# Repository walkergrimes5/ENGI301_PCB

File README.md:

# ENGI301_PCB
PCB design files for ENGI 301 project 2

This project builds on the work I started earlier this year (2018). I am continuing to implement a Octavo PocketBeagle board as the primary flight controller for a 210mm quad copter. The PocketBeagle is not meant specifically for this task, and, as such, is missing several critical components required for flight and autonomous control. Specifically, the board lacks an accelerometer/gyroscope, a altimeter, a GPS connection point, and proper motor headers. The goal of this project is to create a cape for the PocketBeagle that upgrades functionality to include these missing components. The cape fits into the profile of the PocketBeagle and allows it to operate as a flight control board for a quad copter. Eventually, this system should be fully compatible with ArduPilot and be a cheap way to implement a small, autonomous drone.

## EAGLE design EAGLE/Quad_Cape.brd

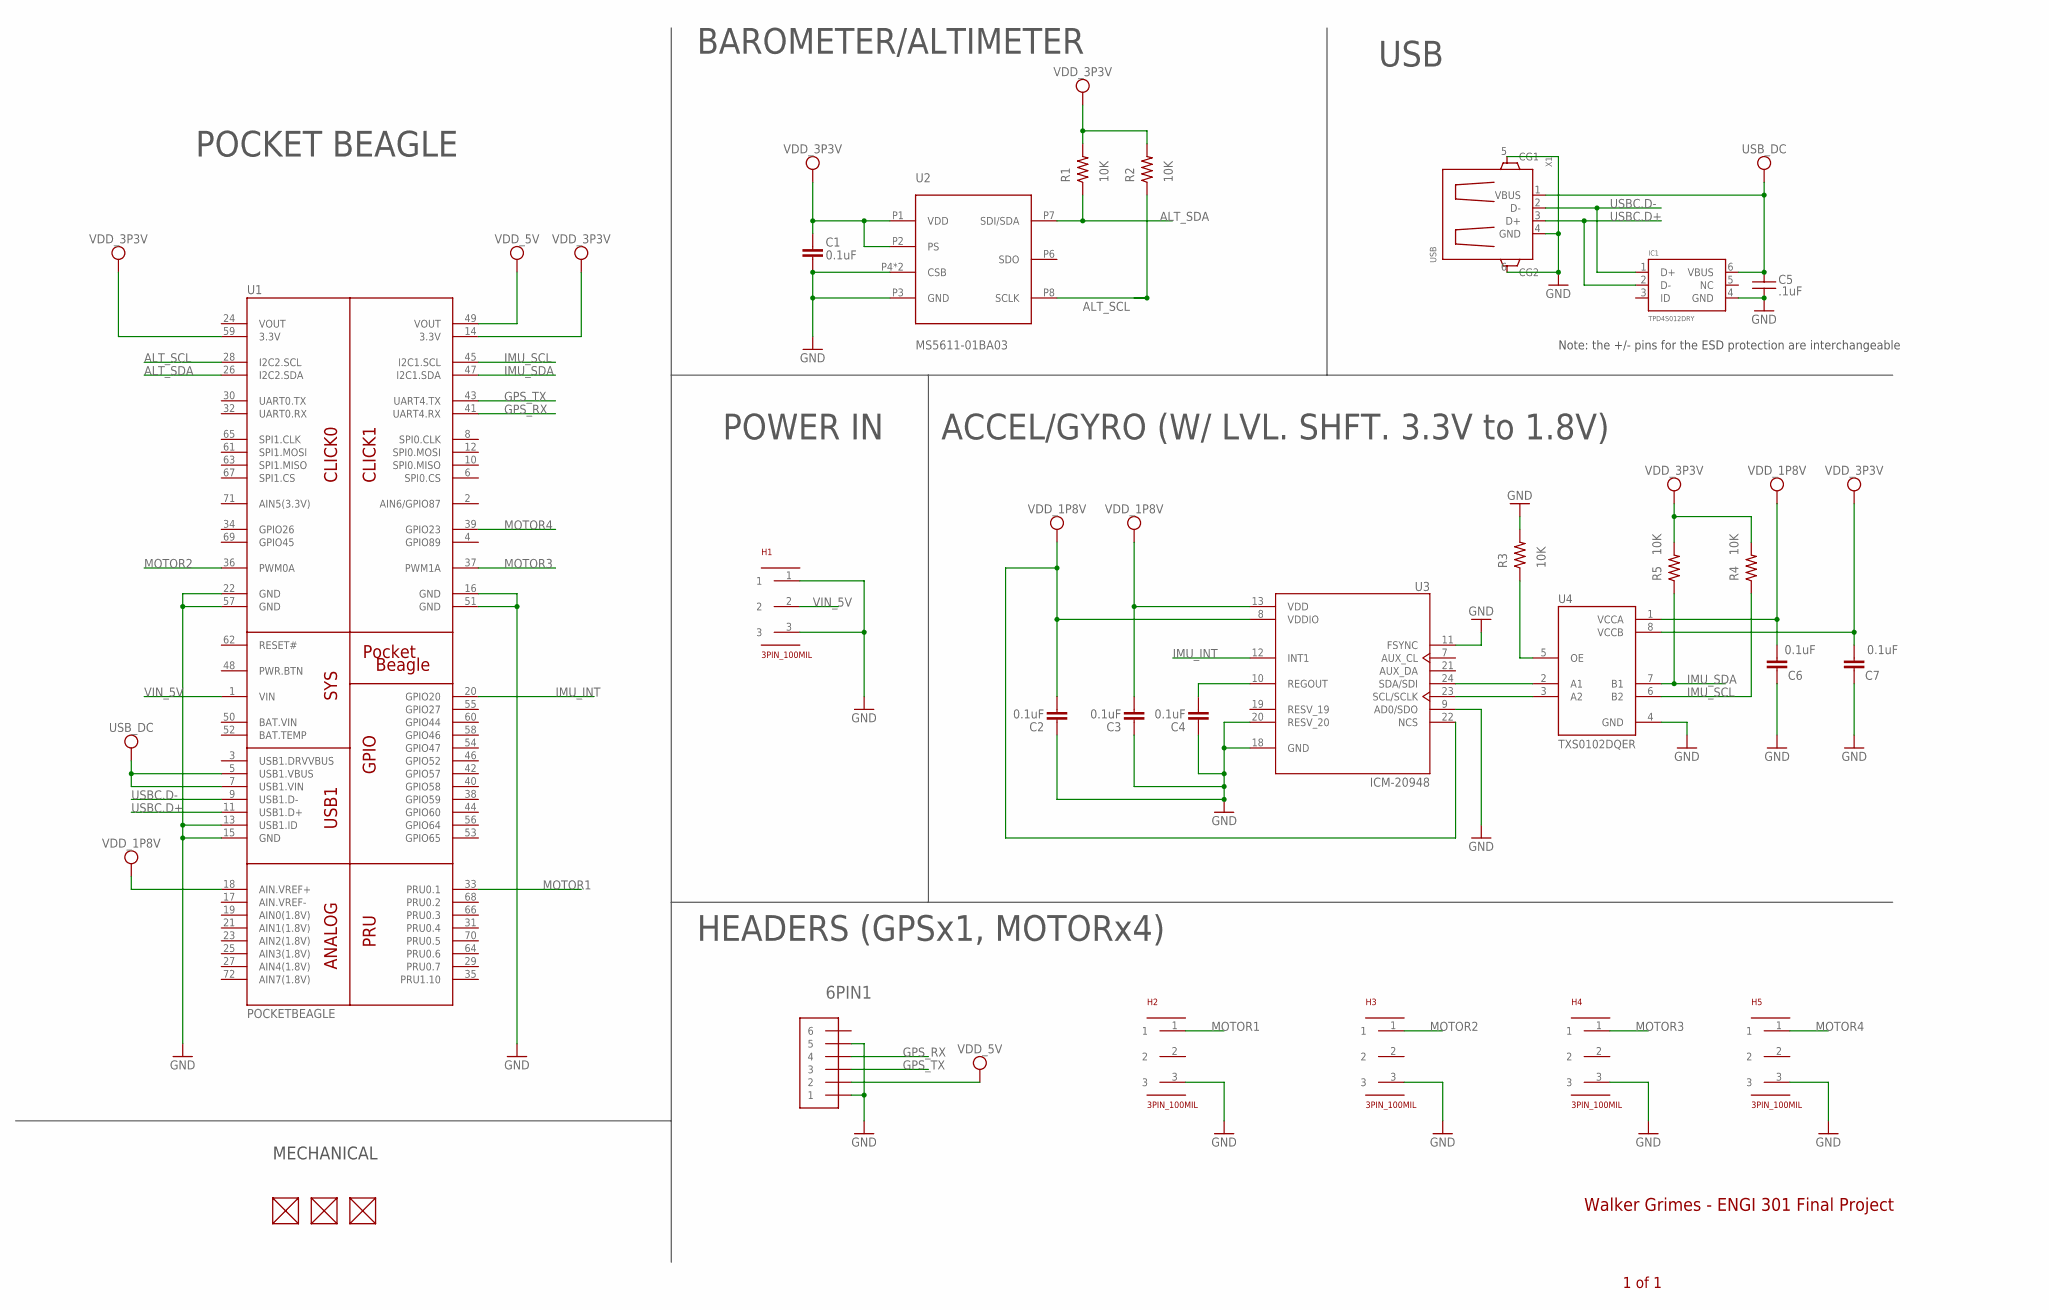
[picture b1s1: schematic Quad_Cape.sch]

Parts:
6PIN1: STRAWSON_EAGLE_LIB_JST_SH_6
C1, C2, C3, C4, C6, C7: 0.1uF; C0603
C5: .1uF; 0402
FUD1, FUD2, FUD3: FIDUCIAL; FIDUCIAL_40MIL
H1, H2, H3, H4, H5: 3PIN_100MIL
IC1: TPD4S012DRY; SON-6(TI)-DRY
R1, R2, R3, R4, R5: 10K; R0603
U1: POCKETBEAGLE
U2: MS5611-01BA03
U3: ICM-20948; QFN40P300X300X105-25N
U4: TXS0102DQER; VOLTAGETRANSLATOR_TXS0102DQER
X1: USB; GHI2_USB_HOST_HORIZONTAL_W/CHASSIS_GND

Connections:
ALT_SCL: R2.1, U1.28 (I2C2.SCL), U2.P8 (SCLK)
ALT_SDA: R1.1, U1.26 (I2C2.SDA), U2.P7 (SDI/SDA)
BAT.VIN: U1.50 (BAT.VIN)
GND: 6PIN1.1, 6PIN1.5, C1.2, C2.1, C3.1, C4.1, C5.2, C6.1, C7.1, H1.1, H1.3, H2.3, H3.3, H4.3, H5.3, IC1.4 (GND), R3.2, U1.13 (USB1.ID), U1.15 (GND), U1.16 (GND), U1.22 (GND), U1.51 (GND), U1.57 (GND), U2.P3 (GND), U2.P4 (CSB), U2.P5 (CSB), U3.9 (AD0/SDO), U3.11 (FSYNC), U3.18 (GND), U3.20 (RESV_20), U4.4 (GND), X1.4 (GND), X1.5 (CG1), X1.6 (CG2)
GPS_RX: 6PIN1.4, U1.41 (UART4.RX)
GPS_TX: 6PIN1.3, U1.43 (UART4.TX)
IMU_INT: U1.20 (GPIO20), U3.12 (INT1)
IMU_SCL: R4.1, U1.45 (I2C1.SCL), U4.6 (B2)
IMU_SDA: R5.1, U1.47 (I2C1.SDA), U4.7 (B1)
MOTOR1: H2.1, U1.33 (PRU0.1)
MOTOR2: H3.1, U1.36 (PWM0A)
MOTOR3: H4.1, U1.37 (PWM1A)
MOTOR4: H5.1, U1.39 (GPIO23)
unnamed: C4.2, U3.10 (REGOUT)
unnamed: R3.1, U4.5 (OE)
unnamed: U3.23 (SCL/SCLK), U4.3 (A2)
unnamed: U3.24 (SDA/SDI), U4.2 (A1)
USBC.D+: IC1.2 (D-), U1.11 (USB1.D+), X1.3 (D+)
USBC.D-: IC1.1 (D+), U1.9 (USB1.D-), X1.2 (D-)
USB_DC: C5.1, IC1.6 (VBUS), U1.5 (USB1.VBUS), U1.7 (USB1.VIN), X1.1 (VBUS)
VDD_1P8V: C2.2, C3.2, C6.2, U1.18 (AIN.VREF+), U3.8 (VDDIO), U3.13 (VDD), U3.22 (NCS), U4.1 (VCCA)
VDD_3P3V: C1.1, C7.2, R1.2, R2.2, R4.2, R5.2, U1.14 (3.3V), U1.59 (3.3V), U2.P1 (VDD), U2.P2 (PS), U4.8 (VCCB)
VDD_5V: 6PIN1.2, U1.49 (VOUT)
VIN_5V: H1.2, U1.1 (VIN)
VOUT: U1.24 (VOUT)

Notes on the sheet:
Walker Grimes - ENGI 301 Final Project
HEADERS (GPSx1, MOTORx4)
BAROMETER/ALTIMETER
USB
ACCEL/GYRO (W/ LVL. SHFT. 3.3V to 1.8V)
POCKET BEAGLE
1 of 1
POWER IN
MECHANICAL
Note: the +/- pins for the ESD protection are interchangeable

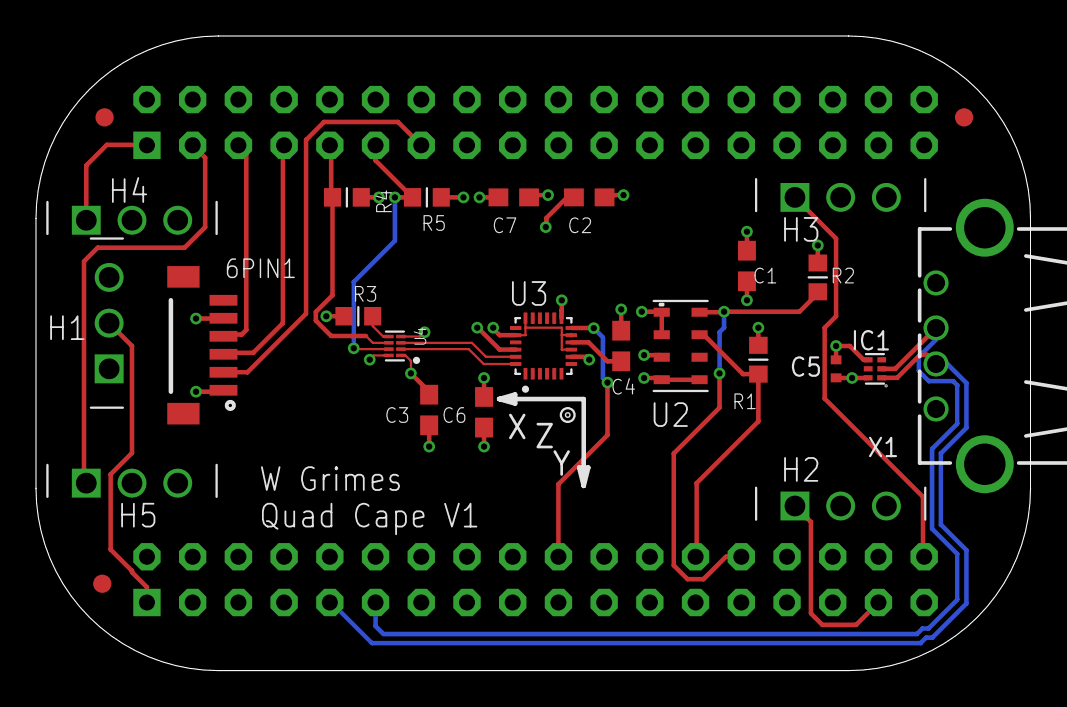
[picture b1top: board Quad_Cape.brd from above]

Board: 4 copper layers, 55.3 x 35.3 mm, 28 parts (0 on the bottom side), 23 nets.

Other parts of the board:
U$5: XYZ_BIG

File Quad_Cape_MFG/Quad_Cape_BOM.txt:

Partlist exported from C:/Users/walke/Documents/Quad_Cape_ENGI301_PCB/EAGLE/Quad_Cape.sch at 12/11/2018 5:32 PM

Qty Value                       Device                      Package                                Parts                  Description                                               AVAILABILITY DESCRIPTION                                                                                            MF                MP          PACKAGE                   PRICE
1   .1uF                        CAPACITOR-(INCH)-0402       0402                                   C5                     Basic SMD ceramic capacitors                                                                                                                                                                                                               
6   0.1uF                       C_C0603                     C0603                                  C1, C2, C3, C4, C6, C7 Capacitor SMD.                                                                                                                                                                                                                             
5   10K                         R_R0603                     R0603                                  R1, R2, R3, R4, R5     RESISTOR, American symbol                                                                                                                                                                                                                  
5   3PIN_100MIL                 3PIN_100MIL                 3PIN_100MIL                            H1, H2, H3, H4, H5                                                                                                                                                                                                                                                
3   FIDUCIAL                    FIDUCIAL                    FIDUCIAL_40MIL                         FUD1, FUD2, FUD3                                                                                                                                                                                                                                                  
1   ICM-20948                   ICM-20948                   QFN40P300X300X105-25N                  U3                     Axis=3 Axis Gyro+3 Axis Accel+Compass. Pin For Pin With m Unavailable   9 Axis=3 Axis Gyro+3 Axis Accel+Compass. Pin For Pin With m                                           TDK InvenSense    ICM-20948   QFN-24 InvenSense         None 
1   MS5611-01BA03               MS5611-01BA03               MS5611-01BA03                          U2                                                                                                                                                                                                                                                                
1   POCKETBEAGLE                POCKETBEAGLE                POCKETBEAGLE                           U1                                                                                                                                                                                                                                                                
1   STRAWSON_EAGLE_LIB_JST_SH_6 STRAWSON_EAGLE_LIB_JST_SH_6 STRAWSON_EAGLE_LIB_JST_SH_6            6PIN1                                                                                                                                                                                                                                                             
1   TPD4S012DRY                 TPD4S012DRYR                SON-6(TI)-DRY                          IC1                                                                                                                                                                                                                                                               
1   TXS0102DQER                 TXS0102DQER                 VOLTAGETRANSLATOR_TXS0102DQER          U4                     IC TRANSLATOR VOLTAGE 8-X2SON                             Unavailable   2-Bit Bidirectional Voltage-Level Shifter for Open-Drain and Push-Pull Application 8-X2SON -40 to 85  Texas Instruments TXS0102DQER XFDFN-8 Texas Instruments None 
1   USB                         GHI2_USB_HOST_W/CHASSIS_GND GHI2_USB_HOST_HORIZONTAL_W/CHASSIS_GND X1

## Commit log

2018-11-27 Added PPT and initialized the library
2018-12-05 Progress on Eagle Library
2018-12-11 BOM and board updates
2018-12-11 Update README.md
    Updated the scope of the ReadMe
2018-12-11 Final changes for V1 board
2018-12-12 Added documentation to project
    Added Gerber files
2018-12-12 Final design tweaks and documentation
2019-01-14 Add files via upload
    Added additional reference material
